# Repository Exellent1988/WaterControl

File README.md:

# WaterControl
ESP32 Project for MEassuring Soil Moisture and opening Valves accordingly

Links, to read!
More about the Sensor : https://thecavepearlproject.org/2020/10/27/hacking-a-capacitive-soil-moisture-sensor-for-frequency-output/

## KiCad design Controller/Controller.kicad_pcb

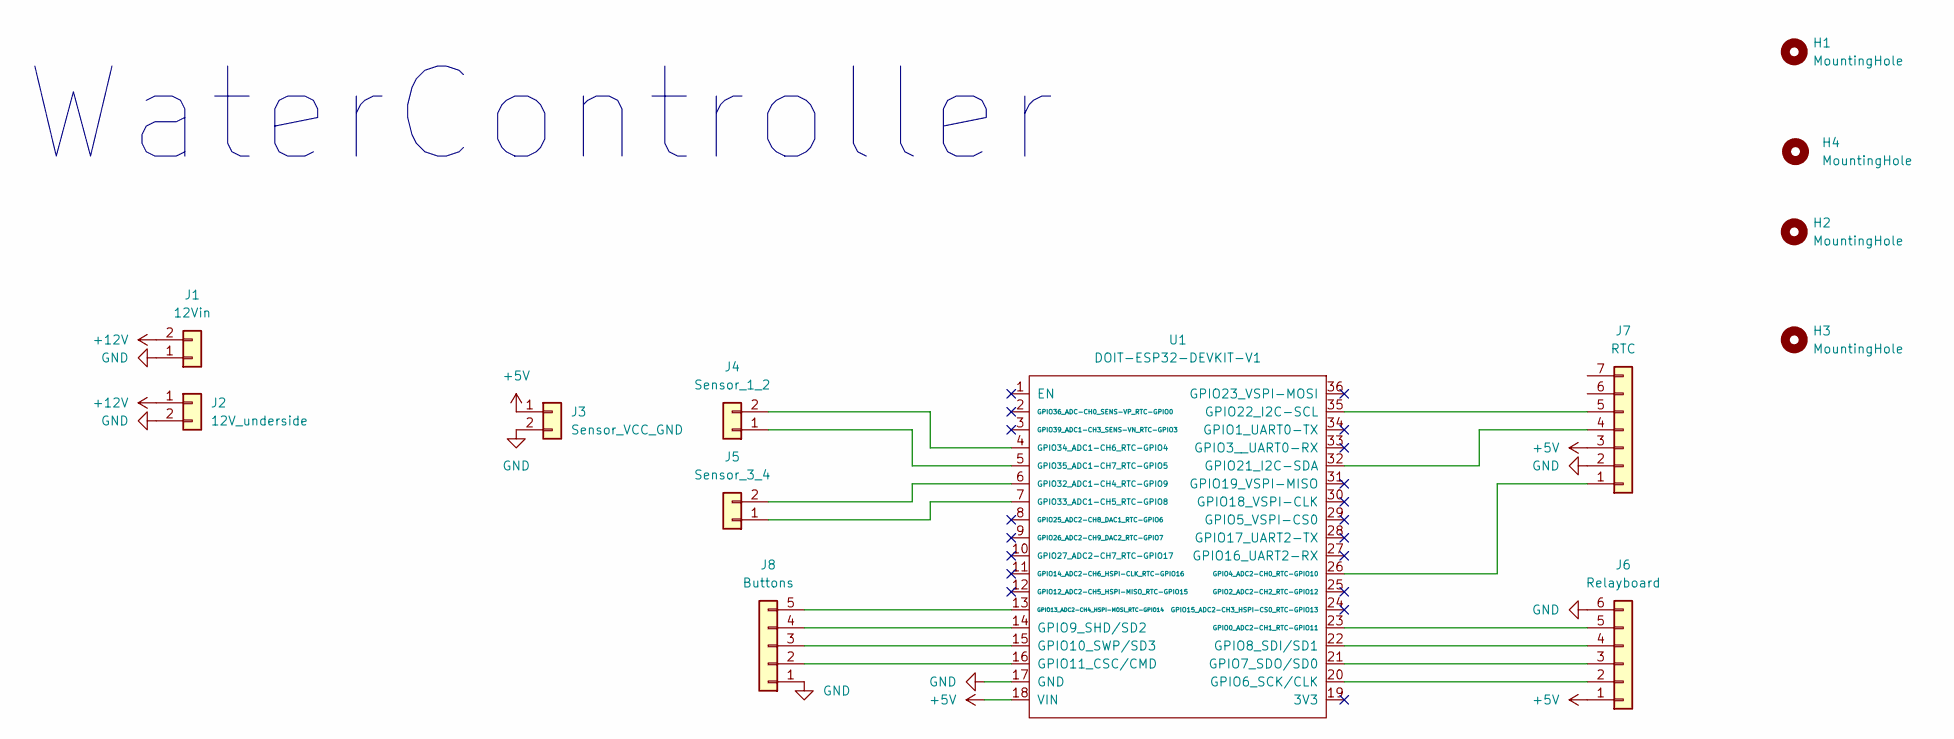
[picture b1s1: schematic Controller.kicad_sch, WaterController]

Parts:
H1, H2, H3, H4: MountingHole; MountingHole_3.2mm_M3_DIN965
J1: 12Vin; TerminalBlock_Altech_AK300-2_P5.00mm
J2: 12V_underside; TerminalBlock_bornier-2_P5.08mm
J3: Sensor_VCC_GND; TerminalBlock_bornier-2_P5.08mm
J4: Sensor_1_2; TerminalBlock_bornier-2_P5.08mm
J5: Sensor_3_4; TerminalBlock_bornier-2_P5.08mm
J6: Relayboard; PinHeader_1x06_P2.54mm_Vertical
J7: RTC; PinSocket_1x07_P2.54mm_Horizontal
J8: Buttons; PinHeader_1x05_P2.54mm_Vertical
U1: DOIT-ESP32-DEVKIT-V1; ESP32-DOIT-DEVKIT

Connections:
+5V: J3.1, J6.1, J7.3, U1.18 (VIN); also elsewhere on the board
+12V: J1.2, J2.1
GND: J1.1, J2.2, J3.2, J6.6, J7.2, J8.1, U1.17 (GND); also elsewhere on the board
unnamed 3: J4.1, U1.5 (GPIO35_ADC1-CH7_RTC-GPIO5); also elsewhere on the board
unnamed 4: J4.2, U1.4 (GPIO34_ADC1-CH6_RTC-GPIO4); also elsewhere on the board
unnamed 5: J5.1, U1.7 (GPIO33_ADC1-CH5_RTC-GPIO8); also elsewhere on the board
unnamed 6: J5.2, U1.6 (GPIO32_ADC1-CH4_RTC-GPIO9); also elsewhere on the board
unnamed 7: J6.2, U1.20 (GPIO6_SCK/CLK); also elsewhere on the board
unnamed 8: J6.3, U1.21 (GPIO7_SDO/SD0); also elsewhere on the board
unnamed 9: J6.4, U1.22 (GPIO8_SDI/SD1); also elsewhere on the board
unnamed 10: J6.5, U1.23 (GPIO0_ADC2-CH1_RTC-GPIO11); also elsewhere on the board
unnamed 11: J7.1, U1.26 (GPIO4_ADC2-CH0_RTC-GPIO10); also elsewhere on the board
unnamed 12: J7.4, U1.32 (GPIO21_I2C-SDA); also elsewhere on the board
unnamed 13: J7.5, U1.35 (GPIO22_I2C-SCL); also elsewhere on the board
unnamed 14: J8.2, U1.16 (GPIO11_CSC/CMD); also elsewhere on the board
unnamed 15: J8.3, U1.15 (GPIO10_SWP/SD3); also elsewhere on the board
unnamed 16: J8.4, U1.14 (GPIO9_SHD/SD2); also elsewhere on the board
unnamed 17: J8.5, U1.13 (GPIO13_ADC2-CH4_HSPI-MOSI_RTC-GPIO14); also elsewhere on the board

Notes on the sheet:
WaterController

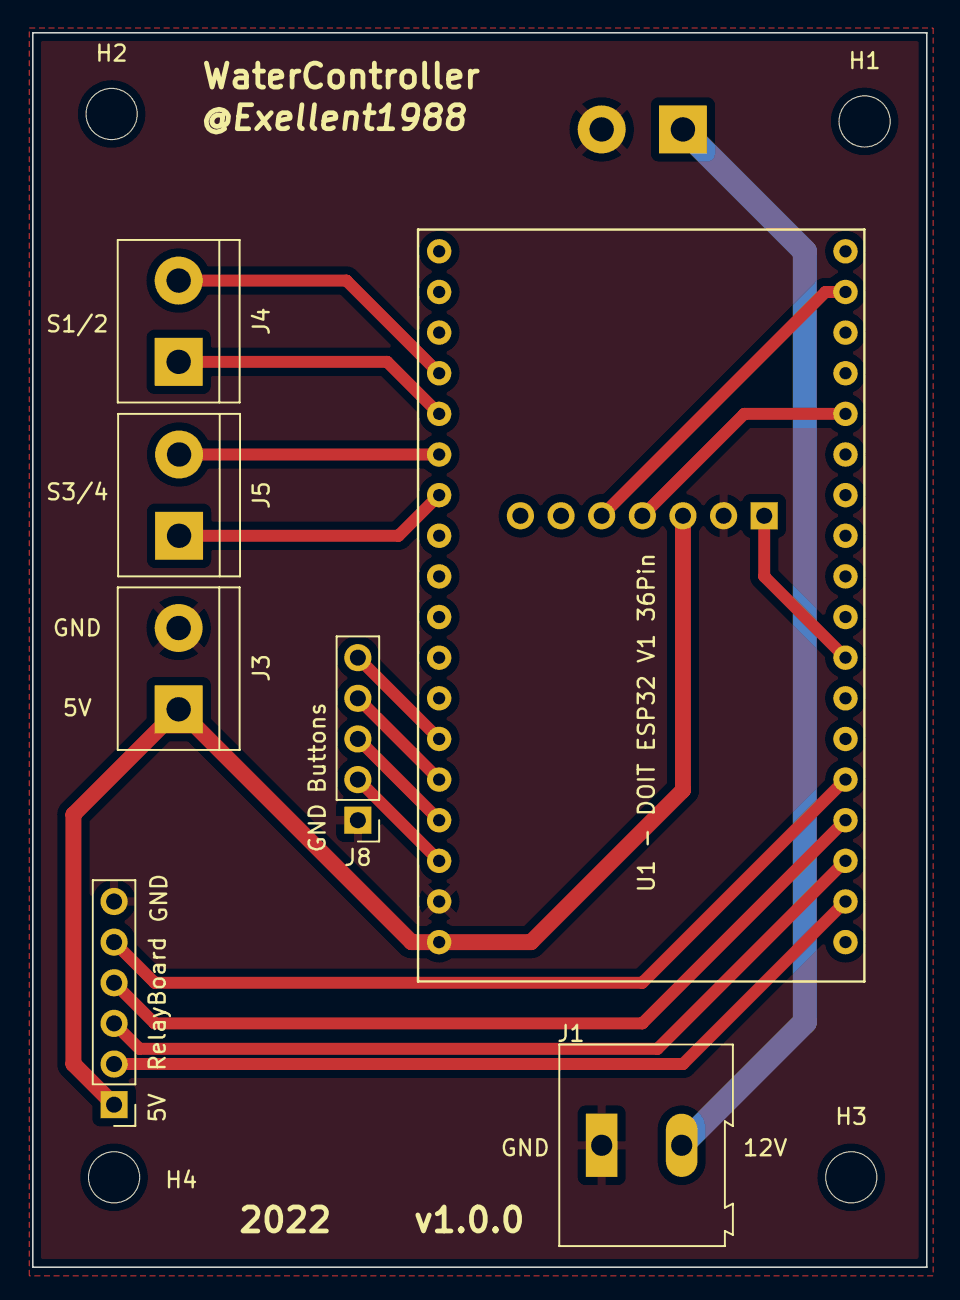
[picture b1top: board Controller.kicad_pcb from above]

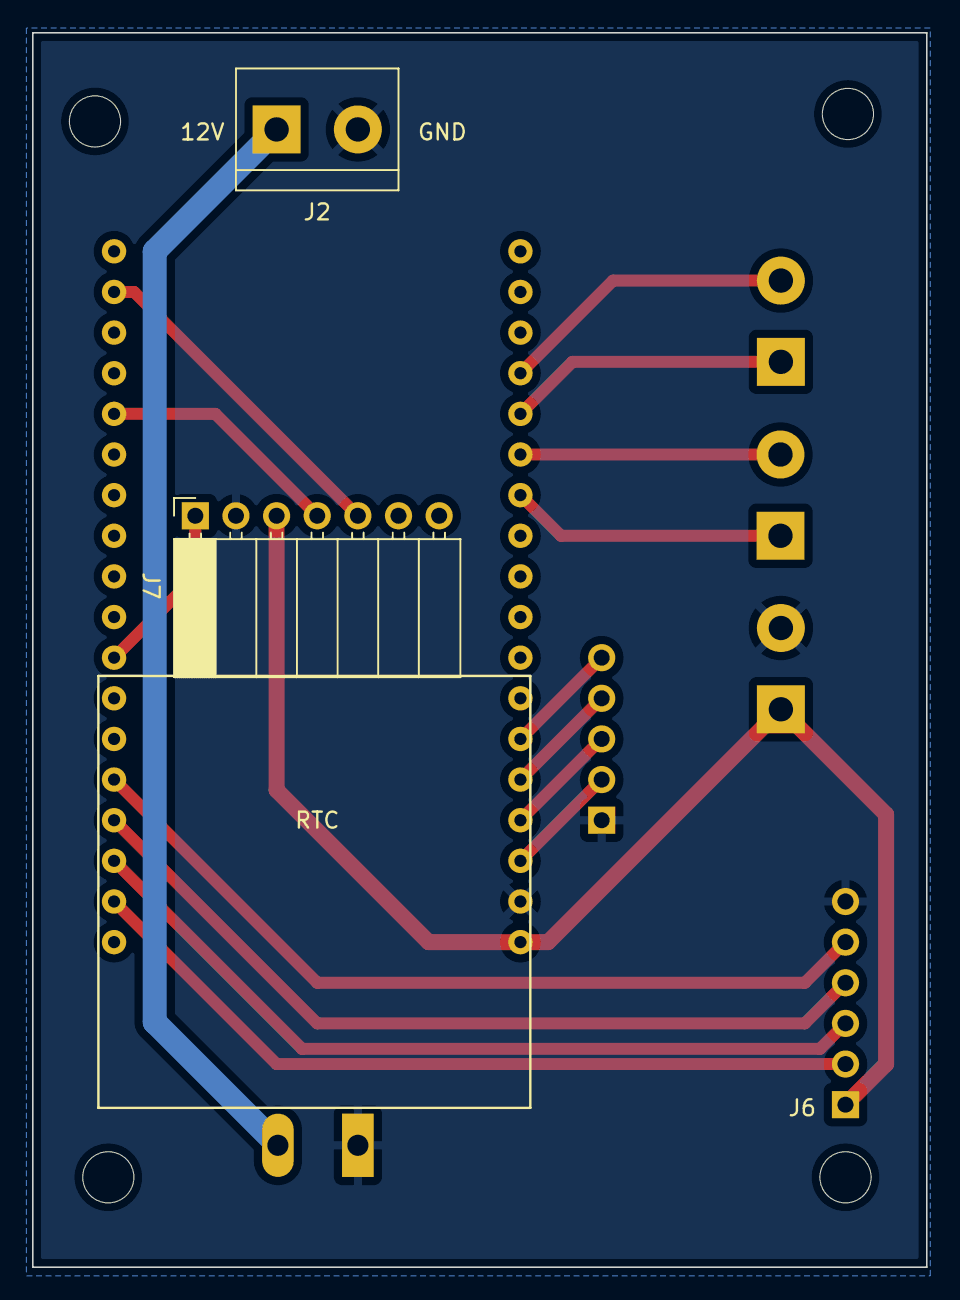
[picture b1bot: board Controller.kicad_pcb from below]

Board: 2 copper layers, 55.9 x 77.2 mm, 13 parts (2 on the bottom side), 18 nets.

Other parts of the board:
U1 - DOIT ESP32 V1 36Pin : DOIT-ESP32-DEVKIT-V1; ESP32-DOIT-DEVKIT

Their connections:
+5V: U1 - DOIT ESP32 V1 36Pin.18 (VIN); also elsewhere on the board
GND: U1 - DOIT ESP32 V1 36Pin.17 (GND); also elsewhere on the board
unnamed 3: U1 - DOIT ESP32 V1 36Pin.5 (GPIO35_ADC1-CH7_RTC-GPIO5); also elsewhere on the board
unnamed 4: U1 - DOIT ESP32 V1 36Pin.4 (GPIO34_ADC1-CH6_RTC-GPIO4); also elsewhere on the board
unnamed 5: U1 - DOIT ESP32 V1 36Pin.7 (GPIO33_ADC1-CH5_RTC-GPIO8); also elsewhere on the board
unnamed 6: U1 - DOIT ESP32 V1 36Pin.6 (GPIO32_ADC1-CH4_RTC-GPIO9); also elsewhere on the board
unnamed 7: U1 - DOIT ESP32 V1 36Pin.20 (GPIO6_SCK/CLK); also elsewhere on the board
unnamed 8: U1 - DOIT ESP32 V1 36Pin.21 (GPIO7_SDO/SD0); also elsewhere on the board
unnamed 9: U1 - DOIT ESP32 V1 36Pin.22 (GPIO8_SDI/SD1); also elsewhere on the board
unnamed 10: U1 - DOIT ESP32 V1 36Pin.23 (GPIO0_ADC2-CH1_RTC-GPIO11); also elsewhere on the board
unnamed 11: U1 - DOIT ESP32 V1 36Pin.26 (GPIO4_ADC2-CH0_RTC-GPIO10); also elsewhere on the board
unnamed 12: U1 - DOIT ESP32 V1 36Pin.32 (GPIO21_I2C-SDA); also elsewhere on the board
unnamed 13: U1 - DOIT ESP32 V1 36Pin.35 (GPIO22_I2C-SCL); also elsewhere on the board
unnamed 14: U1 - DOIT ESP32 V1 36Pin.16 (GPIO11_CSC/CMD); also elsewhere on the board
unnamed 15: U1 - DOIT ESP32 V1 36Pin.15 (GPIO10_SWP/SD3); also elsewhere on the board
unnamed 16: U1 - DOIT ESP32 V1 36Pin.14 (GPIO9_SHD/SD2); also elsewhere on the board
unnamed 17: U1 - DOIT ESP32 V1 36Pin.13 (GPIO13_ADC2-CH4_HSPI-MOSI_RTC-GPIO14); also elsewhere on the board

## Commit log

2021-06-12 inital Version
2021-06-12 Switched to SPIFFS and fixed some Stuff
2021-06-12 better Logs
2021-06-15 esp8266 implemented
2021-06-15 diverser scheiß, aber esp32 UI will nicht
2021-06-30 so timer gedöns und so
2021-06-30 timer zuordnung fixed
2021-06-30 timer var fixed
2021-06-30 debugging timerbased events
2022-03-16 starting to add ADC
2022-03-16 i guess switch to ESP-IOT Framework
2022-03-16 starting to switfch to ESP-IOT Framework
2022-03-16 espasync ota moved to lib
2022-03-17 added lib to project
2022-03-17 remove esp32 functionality, added adc lib and functions, added analog reads with adc
2022-03-21 tryed pin definitios
2022-03-21 added submodule hopefully correct
2022-03-21 switched submodule url
2022-03-30 esp32 is back in game
2022-03-31 ignore .DS_Store files
2022-03-31 different esp dev boards ( ips for OTA)
2022-03-31 lots of dev, but timers are still not working :/
2022-04-10 added Buttons and switched ValveFuinction to Switch, and fixed some timer stuff
2022-04-10 changed Redame with Links
2022-04-10 added Controller Board Layout
2022-04-10 changed PCB Layout
2022-04-10 switched 12V input pins for better routing
2022-04-10 fix gnd connection
2022-04-10 added RC Lib and changed BUttonfunction to ValveToggle
2022-04-10 added Silkscreens, GND Polygons & more
2022-04-10 fixed some layout stuff -pcb
2022-04-12 final PCB Layout rev 1.0
2022-04-15 added MQTT lib
2022-04-15 first mqtt implementation
2022-04-15 first options_file load implementation
2022-04-15 some more improvements
2023-07-09 ip fix
2023-07-09 maybe littleFS fix
2023-07-09 update to 2023, now it builds
2023-07-09 cleanup and config added
2023-07-09 fixed a little typo
2023-07-09 cleanup
2023-07-09 new pins
2023-07-09 trying to get it back running :/
2023-07-10 wroking data env for eps32
2023-07-10 still testing
